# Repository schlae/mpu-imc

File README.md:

# Roland MPU-IMC Clone

**Warning: There is not enough information in this repository to build your
own card. The microcontroller, IC3, has not been dumped, and the logic in
the gate array chip, IC2, is unknown.**

Based on information available in the MPU-IMC service manual, here is an
exact copy of the board layout. The MIDI Processing Unit is a way to connect
digital musical instruments to a computer using the IBM MCA bus.

Further details on the card are available [here](http://ohlandl.ipv7.net/sound/Roland_MPU-IMC.html).

There are two versions of this board in this repository. The first is a clone
of the stock MPU-IMC. The second is a version that incorporates the circuitry
of the external breakout box normally required for the MPU-IMC, including
the optocoupler required by the MIDI specification.

If you're not sure which board you want to build, choose the modified card.
It has several advantages:

1. You will not need the external Roland breakout box.
2. You can use the card bracket from a common IBM token-ring network card.
3. The DE-9 connector uses the more common footprint.

There are some important caveats with this board set:

1. IC2, the HG62E08, is a gate array chip customized by Roland. Think of it
like a small CPLD but hard coded in ROM. I have no information on the internal
schematic. Beware: not all HG62E08 parts will implement the same exact functions.
Look for a Roland house part number, and make sure they match.
2. IC3, the HD6801VD855P, is a custom mask-programmed microcontroller that
runs the whole show. I have no ROM for this microcontroller.
Before paying for expensive PC boards, make sure you have these chips first!
3. The original (but **NOT** the modded card) has been built and works, see this
[thread on Vogons](https://www.vogons.org/viewtopic.php?f=62&t=77197). The
previous revision accidentally swapped pins 26 and 25 on IC3. This has been
corrected for both the original and the modded card.

For fabrication, use a 2-layer process. You must specify a 30-degree edge bevel,
other angles are probably OK but **do not fab without a bevel at all because
this may damage your MCA bus connectors!** Technically you should get hard gold
for the edge fingers, but that's usually expensive and immersion gold works
just fine.

## MPU-IMC (Plain)

Following are reference materials for your convenience.

[Schematic](https://github.com/schlae/mpu-imc/blob/master/StockCard/RolandMpuImc.pdf)

[Bill of materials](https://github.com/schlae/mpu-imc/blob/master/StockCard/RolandMpuImc.csv)

[Fab files](https://github.com/schlae/mpu-imc/raw/master/StockCard/fab/RolandMpuImc.zip)

**Please note that the DE-9 connector is NOT the standard connector commonly
available**--the distance between the mounting holes and the front plane of
the connector is somewhat larger than usual. You may have to search surplus
sources to find one that will fit, or modify the footprint.

## MPU-IMC (Modified)

Following are reference materials for your convenience.

[Schematic](https://github.com/schlae/mpu-imc/blob/master/ModdedCard/RolandMpuImcMod.pdf)

[Bill of materials](https://github.com/schlae/mpu-imc/blob/master/ModdedCard/RolandMpuImcMod.csv)

[Fab files](https://github.com/schlae/mpu-imc/raw/master/ModdedCard/fab/RolandMpuImcMod.zip)

The DE-9 connector uses the industry standard footprint and is readily available from Mouser.
It's been relocated so that the card bracket from an IBM token ring network card (74F9321)
will fit.

# License

This work is licensed under a Creative Commons Attribution 4.0 International License. See [https://creativecommons.org/licenses/by/4.0/](https://creativecommons.org/licenses/by/4.0/).

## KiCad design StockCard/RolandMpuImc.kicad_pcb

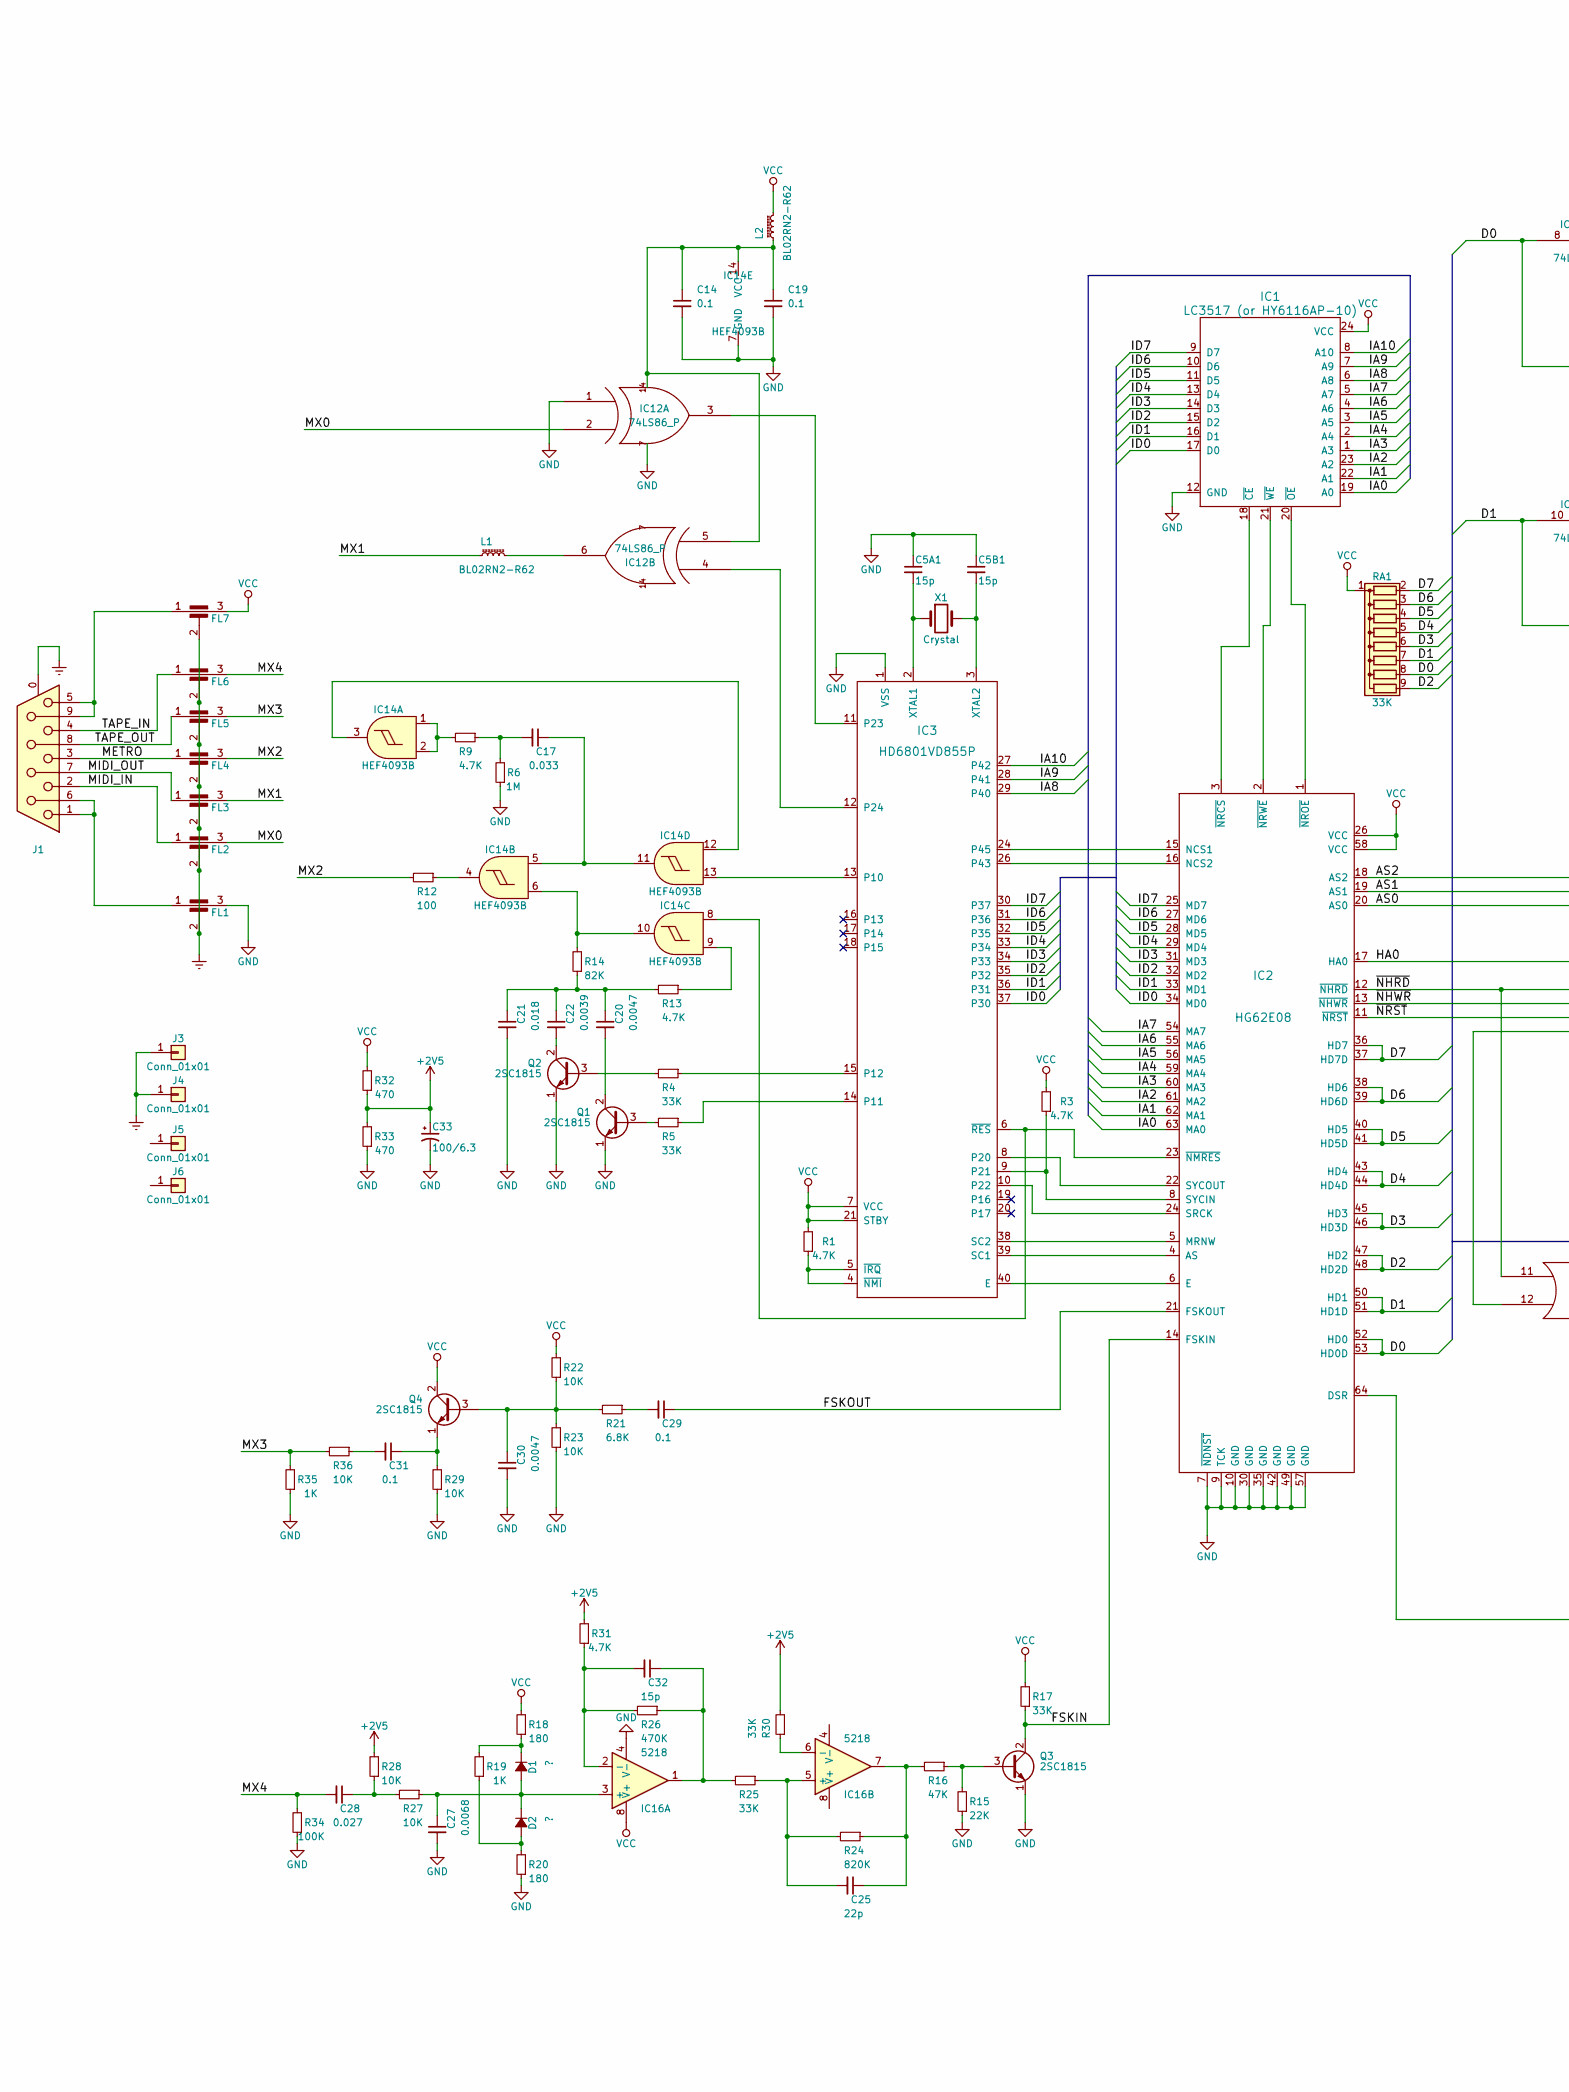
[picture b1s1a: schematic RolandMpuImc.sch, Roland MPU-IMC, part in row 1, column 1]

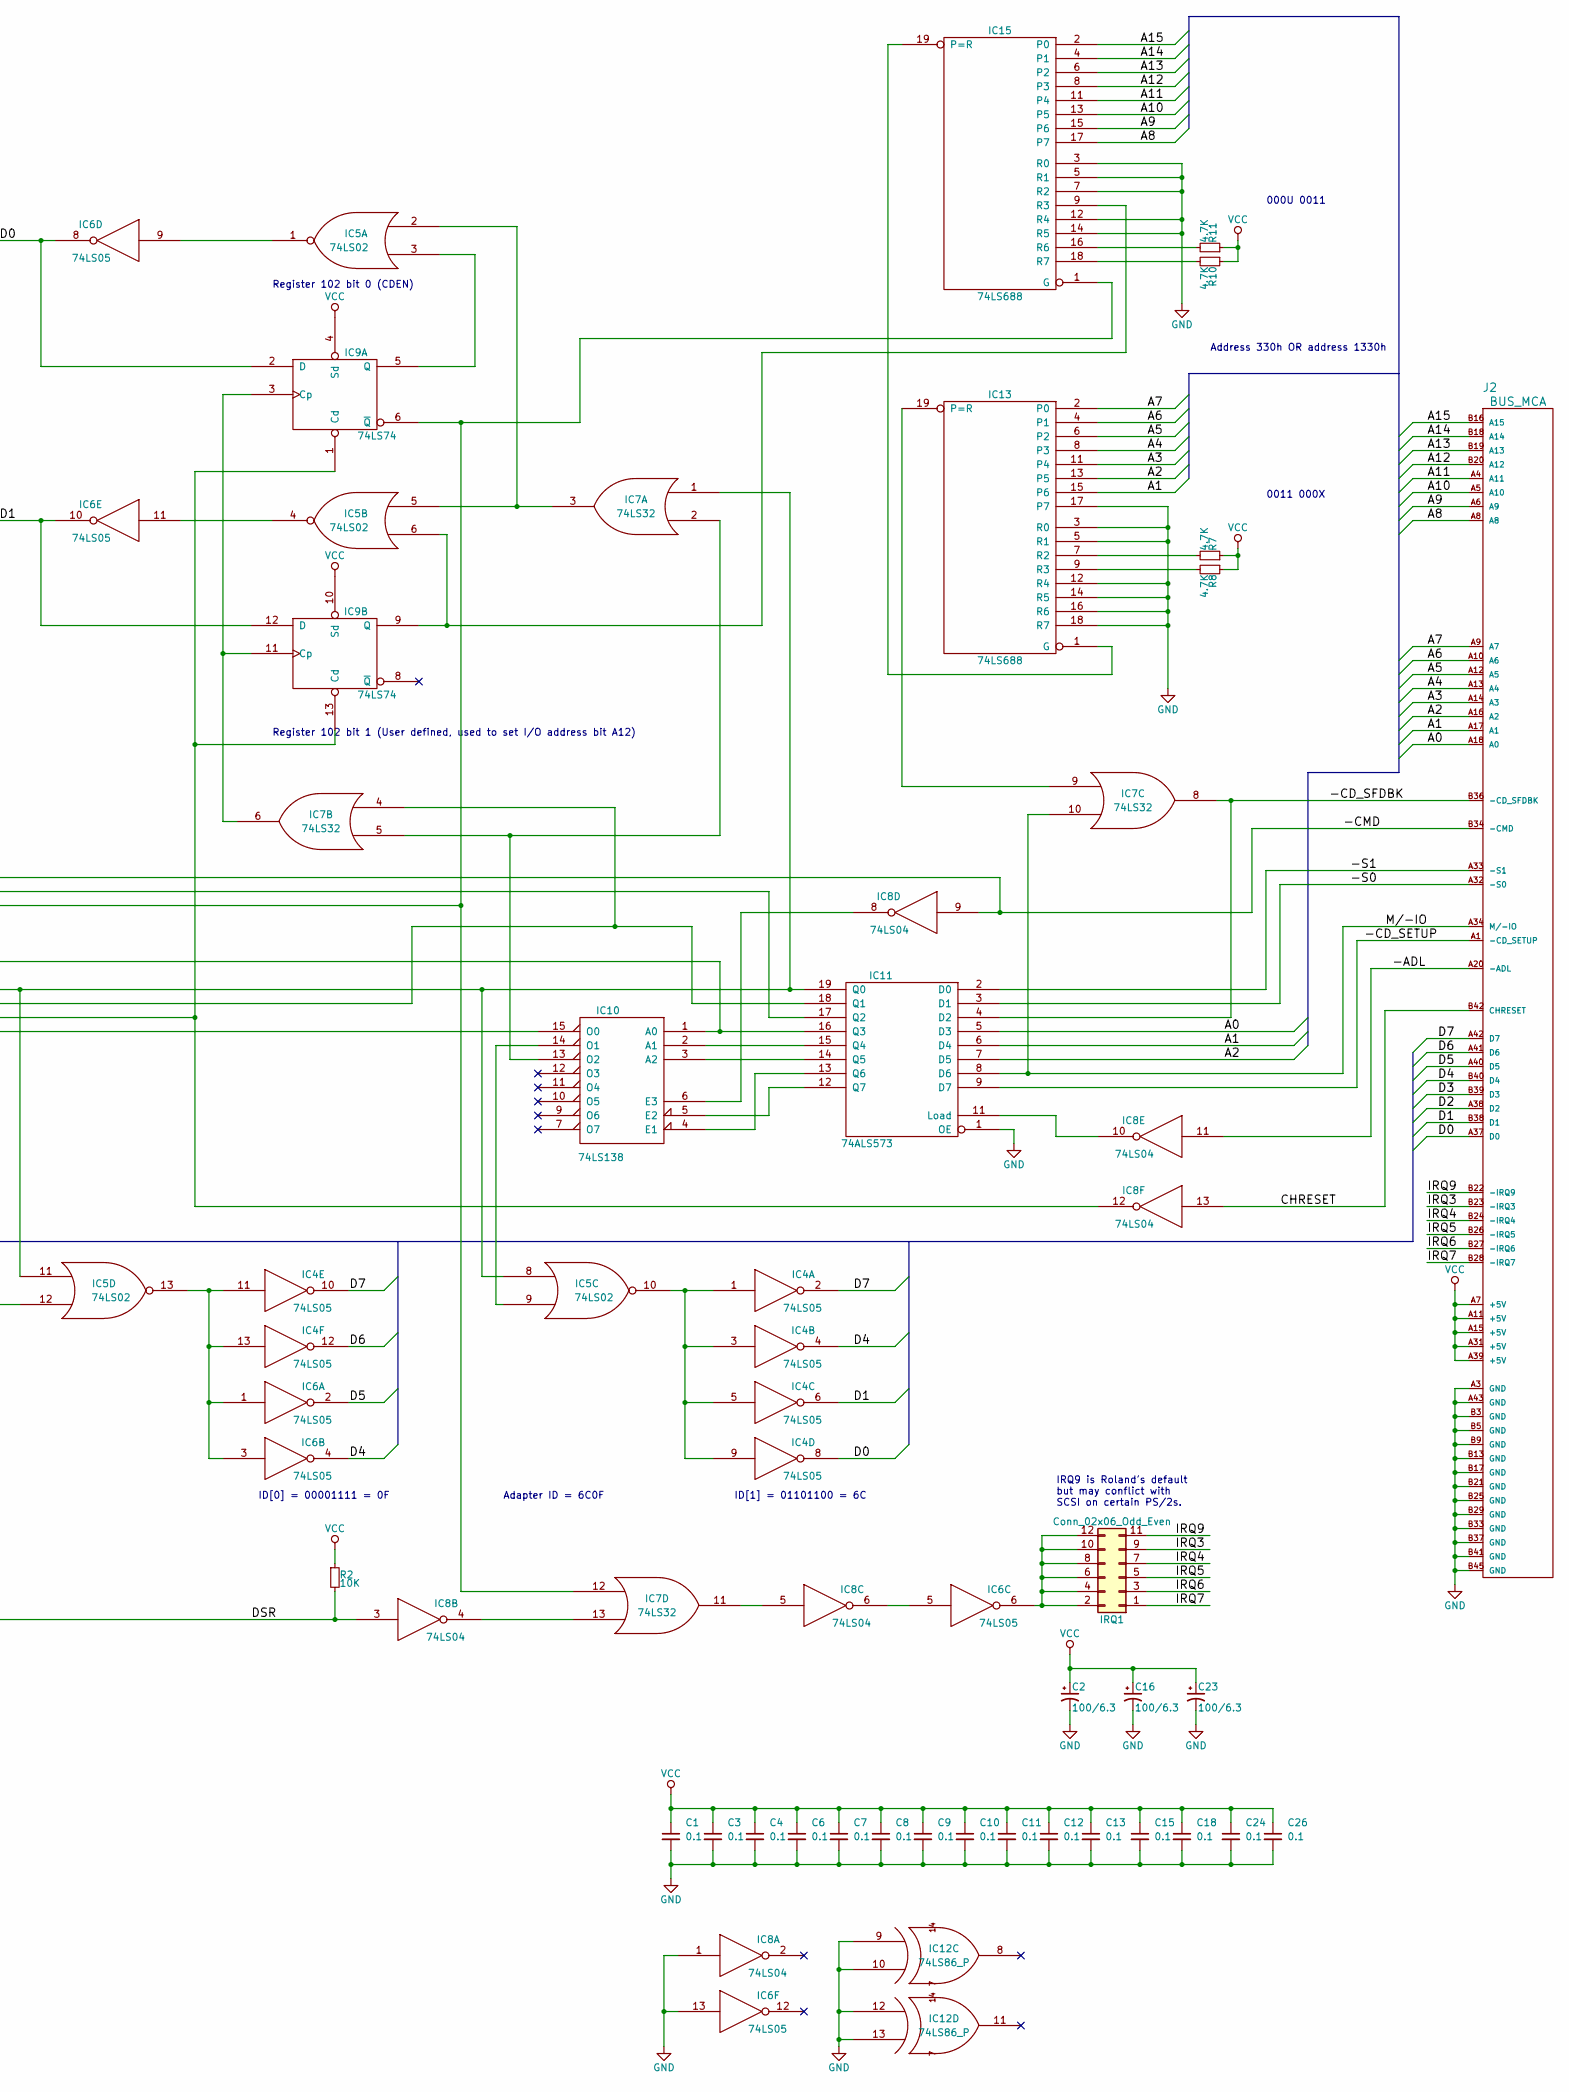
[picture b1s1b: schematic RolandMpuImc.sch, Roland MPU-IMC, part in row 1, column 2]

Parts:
C1, C3, C4, C6, C7, C8, C9, C10, C11, C12, C13, C14, C15, C18, C19, C24, C26, C29, C31: 0.1; C_DISC_200; Mouser 581-SR215E104MAT
C2, C16, C23, C33: 100/6.3; C_RADIAL_200_P; Mouser ECA-0JM101B
C5A1, C5B1, C32: 15p; C_DISC_200; Mouser 581-SR211A150KAR
C17: 0.033; C_DISC_200; Mouser 581-SR215C333K
C20, C30: 0.0047; C_DISC_200; Mouser 581-SR215C472KAA
C21: 0.018; C_DISC_200; Mouser 581-SR215C153KAR
C22: 0.0039; C_DISC_200; Mouser 581-SR215C332KAR
C25: 22p; C_DISC_200; Mouser 581-SR215A220KARTR1
C27: 0.0068; C_DISC_200; Mouser 581-SR215C682KAR
C28: 0.027; C_DISC_200; Mouser 581-SR211E273M
D1, D2: ?; D_200; Mouser 512-1N4148
FL1, FL2, FL3, FL4, FL5, FL6, FL7: EMI_Filter_C; FILT_200; Mouser 652-EMI101T-RC
IC1: LC3517 (or HY6116AP-10); DIP254P1524X635-24
IC2: HG62E08; TQFP-64
IC3: HD6801VD855P; DIP254P1524X635-40
IC4, IC6: 74LS05; DIP254P762X635-14; Mouser 595-SN74LS05N
IC5: 74LS02; DIP254P762X635-14; Mouser 595-SN74LS02N
IC7: 74LS32; DIP254P762X635-14; Mouser 595-SN74LS32N
IC8: 74LS04; DIP254P762X635-14; Mouser 595-SN74LS04N
IC9: 74LS74; DIP254P762X635-14; Mouser SN74LS74AN
IC10: 74LS138; DIP254P762X635-16; Mouser 595-SN74LS138N
IC11: 74ALS573; DIP254P762X635-20; Mouser 595-SN74ALS573CN
IC12: 74LS86_P; DIP254P762X635-14; Mouser 595-SN74LS86AN
IC13, IC15: 74LS688; DIP254P762X635-20; Mouser 595-SN74LS688N
IC14: HEF4093B; DIP254P762X635-14; Mouser 595-CD4093BE
IC16: 5218; DIP254P762X635-8; Mouser 595-TLV2362IP
IRQ1: Conn_02x06_Odd_Even; Pin_Header_Straight_2x06_Pitch2.54mm
J1: DB9_Female_MountingHoles; DE-9; Mouser 523-L77SDE09S1ACH4F
J2: BUS_MCA; BUS_MCA_ROLAND
J3, J4, J5, J6: Conn_01x01; MountingHole_3.2mm_M3
L1, L2: BL02RN2-R62; FERR_200; Mouser 81-BL03RN2R1P1A
Q1, Q2, Q3, Q4: 2SC1815; Q_200_J; Mouser 610-2SC1815
R1, R3, R7, R8, R9, R10, R11, R13, R31: 4.7K; R_AXIAL_200; Mouser 603-CFR-12JB-52-4K7
R2, R22, R23, R27, R28, R29, R36: 10K; R_AXIAL_200; Mouser 603-CFR-12JB-52-10K
R4, R5, R17, R25, R30: 33K; R_AXIAL_200; Mouser 603-CFR-12JB-52-33K
R6: 1M; R_AXIAL_200; Mouser 603-CFR-12JB-52-1M
R12: 100; R_AXIAL_200; Mouser 603-CFR-12JB-52-100R
R14: 82K; R_AXIAL_200; Mouser 603-CFR-12JB-52-82K
R15: 22K; R_AXIAL_200; Mouser 603-CFR-12JB-52-22K
R16: 47K; R_AXIAL_200; Mouser 603-CFR-12JB-52-47K
R18, R20: 180; R_AXIAL_200; Mouser 603-CFR-12JB-52-180R
R19, R35: 1K; R_AXIAL_200; Mouser 603-CFR-12JB-52-1K
R21: 6.8K; R_AXIAL_200; Mouser 603-CFR-12JB-52-6K8
R24: 820K; R_AXIAL_200; Mouser 603-CFR-12JB-52-820K
R26: 470K; R_AXIAL_200; Mouser 603-CFR-12JR-52-470K
R32, R33: 470; R_AXIAL_200; Mouser 603-CFR-12JB-52-470R
R34: 100K; R_AXIAL_200; Mouser 603-CFR-12JB-52-100K
RA1: 33K; R_Array_SIP9; Mouser 652-4609X-1LF-33K
X1: Crystal; Y_200; Mouser 520-HCU400-20X

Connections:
+2V5: C33.1, R28.2, R30.2, R31.2, R32.1, R33.2
/-ADL: IC8.11, J2.A20 (-ADL)
/-CD_SETUP: IC11.9 (D7), J2.A1 (-CD_SETUP)
/-CD_SFDBK: IC7.8, IC11.4 (D2), J2.B36 (-CD_SFDBK)
/-CMD: IC2.18 (AS2), IC8.9, J2.B34 (-CMD)
/-S0: IC11.3 (D1), J2.A32 (-S0)
/-S1: IC11.2 (D0), J2.A33 (-S1)
/A0: IC11.5 (D3), J2.A18 (A0)
/A1: IC11.6 (D4), IC13.15 (P6), J2.A17 (A1)
/A2: IC11.7 (D5), IC13.13 (P5), J2.A16 (A2)
/A3: IC13.11 (P4), J2.A14 (A3)
/A4: IC13.8 (P3), J2.A13 (A4)
/A5: IC13.6 (P2), J2.A12 (A5)
/A6: IC13.4 (P1), J2.A10 (A6)
/A7: IC13.2 (P0), J2.A9 (A7)
/A8: IC15.17 (P7), J2.A8
/A9: IC15.15 (P6), J2.A6 (A9)
/A10: IC15.13 (P5), J2.A5 (A10)
/A11: IC15.11 (P4), J2.A4 (A11)
/A12: IC15.8 (P3), J2.B20 (A12)
/A13: IC15.6 (P2), J2.B19 (A13)
/A14: IC15.4 (P1), J2.B18 (A14)
/A15: IC15.2 (P0), J2.B16 (A15)
/AS0: IC2.20 (AS0), IC7.12, IC9.6 (~Q), IC15.1 (G)
/AS1: IC2.19 (AS1), IC11.17 (Q2)
/CHRESET: IC8.13, J2.B42 (CHRESET)
/D0: IC2.52 (HD0), IC2.53 (HD0D), IC4.8, IC6.8, IC9.2 (D), J2.A37 (D0), RA1.8 (R7)
/D1: IC2.50 (HD1), IC2.51 (HD1D), IC4.6, IC6.10, IC9.12 (D), J2.B38 (D1), RA1.7 (R6)
/D2: IC2.47 (HD2), IC2.48 (HD2D), J2.A38 (D2), RA1.9 (R8)
/D3: IC2.45 (HD3), IC2.46 (HD3D), J2.B39 (D3), RA1.6 (R5)
/D4: IC2.43 (HD4), IC2.44 (HD4D), IC4.4, IC6.4, J2.B40 (D4), RA1.5 (R4)
/D5: IC2.40 (HD5), IC2.41 (HD5D), IC6.2, J2.A40 (D5), RA1.4 (R3)
/D6: IC2.38 (HD6), IC2.39 (HD6D), IC4.12, J2.A41 (D6), RA1.3 (R2)
/D7: IC2.36 (HD7), IC2.37 (HD7D), IC4.2, IC4.10, J2.A42 (D7), RA1.2 (R1)
/DSR: IC2.64 (DSR), IC8.3, R2.2
/FSKIN: IC2.14 (FSKIN), Q3.2 (C), R17.1
/FSKOUT: C29.1, IC2.21 (FSKOUT)
/HA0: IC2.17 (HA0), IC10.1 (A0), IC11.16 (Q3)
/IA0: IC1.19 (A0), IC2.63 (MA0)
/IA1: IC1.22 (A1), IC2.62 (MA1)
/IA2: IC1.23 (A2), IC2.61 (MA2)
/IA3: IC1.1 (A3), IC2.60 (MA3)
/IA4: IC1.2 (A4), IC2.59 (MA4)
/IA5: IC1.3 (A5), IC2.56 (MA5)
/IA6: IC1.4 (A6), IC2.55 (MA6)
/IA7: IC1.5 (A7), IC2.54 (MA7)
/IA8: IC1.6 (A8), IC3.29 (P40)
/IA9: IC1.7 (A9), IC3.28 (P41)
/IA10: IC1.8 (A10), IC3.27 (P42)
/ID0: IC1.17 (D0), IC2.34 (MD0), IC3.37 (P30)
/ID1: IC1.16 (D1), IC2.33 (MD1), IC3.36 (P31)
/ID2: IC1.15 (D2), IC2.32 (MD2), IC3.35 (P32)
/ID3: IC1.14 (D3), IC2.31 (MD3), IC3.34 (P33)
/ID4: IC1.13 (D4), IC2.29 (MD4), IC3.33 (P34)
/ID5: IC1.11 (D5), IC2.28 (MD5), IC3.32 (P35)
/ID6: IC1.10 (D6), IC2.27 (MD6), IC3.31 (P36)
/ID7: IC1.9 (D7), IC2.25 (MD7), IC3.30 (P37)
/IRQ3: IRQ1.9, J2.B23 (-IRQ3)
/IRQ4: IRQ1.7, J2.B24 (-IRQ4)
/IRQ5: IRQ1.5, J2.B26 (-IRQ5)
/IRQ6: IRQ1.3, J2.B27 (-IRQ6)
/IRQ7: IRQ1.1, J2.B28 (-IRQ7)
/IRQ9: IRQ1.11, J2.B22 (-IRQ9)
/M/-IO: IC7.10, IC11.8 (D6), J2.A34 (M/-IO)
/METRO: FL4.1, J1.3
/MIDI_IN: FL2.1, J1.2
/MIDI_OUT: FL3.1, J1.7
/MX0: FL2.3, IC12.2 (IN2)
/MX1: FL3.3, L1.1
/MX2: FL4.3, R12.2
/MX3: FL5.3, R35.2, R36.2
/MX4: C28.2, FL6.3, R34.2
/TAPE_IN: FL6.1, J1.4
/TAPE_OUT: FL5.1, J1.8
/~NHRD: IC2.12 (~NHRD), IC5.8, IC5.11, IC7.1, IC11.19 (Q0)
/~NHWR: IC2.13 (~NHWR), IC7.4, IC11.18 (Q1)
/~NRST: IC2.11 (~NRST), IC8.12, IC9.1 (Cd), IC9.13 (Cd)
Earth: FL1.2, FL2.2, FL3.2, FL4.2, FL5.2, FL6.2, FL7.2, J1.0 (PAD), J3.1, J4.1
GND: C1.2, C2.2, C3.2, C4.2, C5A1.1, C5B1.1, C6.2, C7.2, C8.2, C9.2, C10.2, C11.2, C12.2, C13.2, C14.2, C15.2, C16.2, C18.2, C19.2, C21.2, C23.2, C24.2, C26.2, C27.2, C30.2, C33.2, FL1.3, IC1.12 (GND), IC2.7 (~NDNST), IC2.9 (TCK), IC2.10 (GND), IC2.30 (GND), IC2.35 (GND), IC2.42 (GND), IC2.49 (GND), IC2.57 (GND), IC3.1 (VSS), IC4.7 (GND), IC5.7 (GND), IC6.7 (GND), IC6.13, IC7.7 (GND), IC8.1, IC8.7 (GND), IC9.7 (GND), IC10.8 (GND), IC11.1 (OE), IC11.10 (GND), IC12.1 (IN1), IC12.7 (GND), IC12.9 (IN1), IC12.10 (IN2), IC12.12 (IN1), IC12.13 (IN2), IC13.3 (R0), IC13.5 (R1), IC13.10 (GND), IC13.12 (R4), IC13.14 (R5), IC13.16 (R6), IC13.17 (P7), IC13.18 (R7), IC14.7 (GND), IC15.3 (R0), IC15.5 (R1), IC15.7 (R2), IC15.10 (GND), IC15.12 (R4), IC15.14 (R5), IC16.4 (V-), J2.A3 (GND), J2.A43 (GND), J2.B3 (GND), J2.B5 (GND), J2.B9 (GND), J2.B13 (GND), J2.B17 (GND), J2.B21 (GND), J2.B25 (GND), J2.B29 (GND), J2.B33 (GND), J2.B37 (GND), J2.B41 (GND), J2.B45 (GND), Q1.1 (E), Q2.1 (E), Q3.1 (E), R6.1, R15.1, R20.1, R23.1, R29.1, R33.1, R34.1, R35.1
unnamed: C5A1.2, IC3.2 (XTAL1), X1.1
unnamed: C5B1.2, IC3.3 (XTAL2), X1.2
unnamed: C14.1, C19.1, IC12.5 (IN2), IC12.14 (VCC), IC14.14 (VCC), L2.1
unnamed: C17.1, IC14.5, IC14.11
unnamed: C17.2, R6.2, R9.1
unnamed: C20.1, C21.1, C22.1, R13.2, R14.1
unnamed: C20.2, Q1.2 (C)
unnamed: C22.2, Q2.2 (C)
unnamed: C25.1, IC16.7, R16.2, R24.1
unnamed: C25.2, IC16.5 (+), R24.2, R25.1
unnamed: C27.1, D1.2 (A), D2.1 (K), IC16.3 (+), R27.1
unnamed: C28.1, R27.2, R28.1
unnamed: C29.2, R21.1
unnamed: C30.1, Q4.3 (B), R21.2, R22.1, R23.2
unnamed: C31.1, Q4.1 (E), R29.2
unnamed: C31.2, R36.1
unnamed: C32.1, IC16.1, R25.2, R26.1
unnamed: C32.2, IC16.2 (-), R26.2, R31.1
unnamed: D1.1 (K), R18.1, R19.2
unnamed: D2.2 (A), R19.1, R20.2
unnamed: FL1.1, J1.1, J1.6
unnamed: FL7.1, J1.5, J1.9
unnamed: IC1.18 (~CE), IC2.3 (~NRCS)
unnamed: IC1.20 (~OE), IC2.1 (~NROE)
unnamed: IC1.21 (~WE), IC2.2 (~NRWE)
unnamed: IC2.4 (AS), IC3.39 (SC1)
unnamed: IC2.5 (MRNW), IC3.38 (SC2)
unnamed: IC2.6 (E), IC3.40 (E)
unnamed: IC2.8 (SYCIN), IC3.9 (P21), R3.1
unnamed: IC2.15 (NCS1), IC3.24 (P45)
unnamed: IC2.16 (NCS2), IC3.26 (P43)
unnamed: IC2.22 (SYCOUT), IC3.8 (P20)
unnamed: IC2.24 (SRCK), IC3.10 (P22)
unnamed: IC3.4 (~NMI), IC3.5 (~IRQ), R1.1
unnamed: IC3.14 (P11), R5.1
unnamed: IC3.15 (P12), R4.1
unnamed: IC4.1, IC4.3, IC4.5, IC4.9, IC5.10
unnamed: IC4.11, IC4.13, IC5.13, IC6.1, IC6.3
unnamed: IC5.1, IC6.9
unnamed: IC5.2, IC5.5, IC7.3
unnamed: IC5.3, IC9.5 (Q)
unnamed: IC5.4, IC6.11
unnamed: IC6.5, IC8.6
unnamed: IC6.6, IRQ1.2, IRQ1.4, IRQ1.6, IRQ1.8, IRQ1.10, IRQ1.12
unnamed: IC7.6, IC9.3 (Cp), IC9.11 (Cp)
unnamed: IC7.11, IC8.5
unnamed: IC7.13, IC8.4
unnamed: IC10.2 (A1), IC11.15 (Q4)
unnamed: IC10.3 (A2), IC11.14 (Q5)
unnamed: IC10.4 (E1), IC11.13 (Q6)
unnamed: IC10.5 (E2), IC11.12 (Q7)
unnamed: IC8.8, IC10.6 (E3)
unnamed: IC7.2, IC7.5, IC10.13 (O2)
unnamed: IC5.9, IC10.14 (O1)
unnamed: IC5.12, IC10.15 (O0)
unnamed: IC8.10, IC11.11 (Load)
unnamed: IC3.11 (P23), IC12.3 (OUT)
unnamed: IC3.12 (P24), IC12.4 (IN1)
unnamed: IC12.6 (OUT), L1.2
unnamed: IC13.1 (G), IC15.19 (P=R)
unnamed: IC13.7 (R2), R7.2
unnamed: IC13.9 (R3), R8.2
unnamed: IC7.9, IC13.19 (P=R)
unnamed: IC14.1, IC14.2, R9.2
unnamed: IC14.4, R12.1
unnamed: IC2.23 (~NMRES), IC3.6 (~RES), IC14.8
unnamed: IC14.9, R13.1
unnamed: IC14.6, IC14.10, R14.2
unnamed: IC14.3, IC14.12
unnamed: IC3.13 (P10), IC14.13
unnamed: IC5.6, IC9.9 (Q), IC15.9 (R3)
unnamed: IC15.16 (R6), R11.2
unnamed: IC15.18 (R7), R10.2
unnamed: IC16.6 (-), R30.1
unnamed: Q1.3 (B), R5.2
unnamed: Q2.3 (B), R4.2
unnamed: Q3.3 (B), R15.2, R16.1
VCC: C1.1, C2.1, C3.1, C4.1, C6.1, C7.1, C8.1, C9.1, C10.1, C11.1, C12.1, C13.1, C15.1, C16.1, C18.1, C23.1, C24.1, C26.1, FL7.3, IC1.24 (VCC), IC2.26 (VCC), IC2.58 (VCC), IC3.7 (VCC), IC3.21 (STBY), IC4.14 (VCC), IC5.14 (VCC), IC6.14 (VCC), IC7.14 (VCC), IC8.14 (VCC), IC9.4 (Sd), IC9.10 (Sd), IC9.14 (VCC), IC10.16 (VCC), IC11.20 (VCC), IC13.20 (VCC), IC15.20 (VCC), IC16.8 (V+), J2.A7 (+5V), J2.A11 (+5V), J2.A15 (+5V), J2.A31 (+5V), J2.A39 (+5V), L2.2, Q4.2 (C), R1.2, R2.1, R3.2, R7.1, R8.1, R10.1, R11.1, R17.2, R18.2, R22.2, R32.2, RA1.1 (common)

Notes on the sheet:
Register 102 bit 0 (CDEN)
Register 102 bit 1 (User defined, used to set I/O address bit A12)
000U 0011
0011 000X
Address 330h OR address 1330h
ID[0] = 00001111 = 0F
ID[1] = 01101100 = 6C
Adapter ID = 6C0F
IRQ9 is Roland's default but may conflict with SCSI on certain PS/2s.

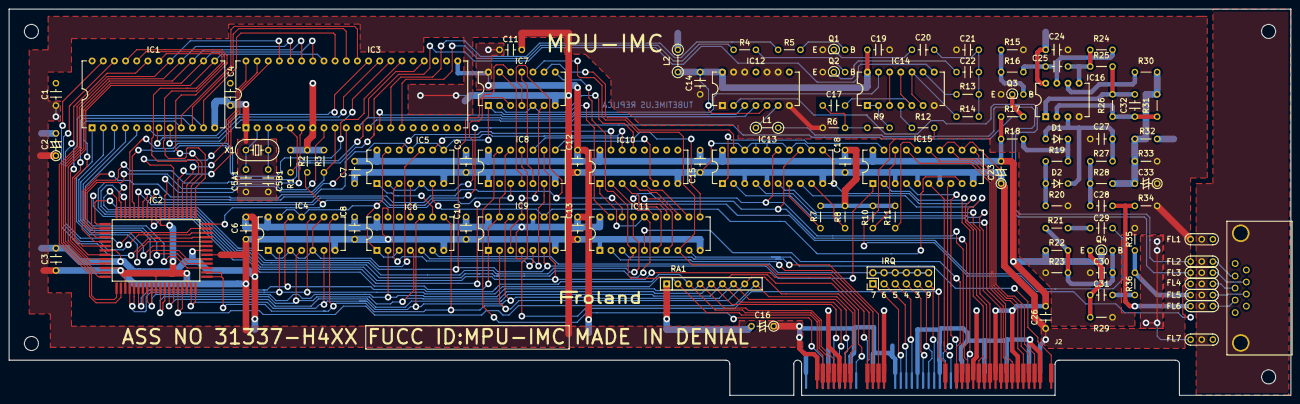
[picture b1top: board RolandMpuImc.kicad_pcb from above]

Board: 2 copper layers, 292.1 x 88.0 mm, 110 parts (0 on the bottom side), 157 nets.

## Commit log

2018-10-15 Initial commit.
2018-10-16 Added files for both cards.
2021-04-15 Fix IC3 pin swap and a few part numbers

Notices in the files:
StockCard/RolandMpuImc.kicad_pcb:
Copyright (C) 2018 Eric Schlaepfer
